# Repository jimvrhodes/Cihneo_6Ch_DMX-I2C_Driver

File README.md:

# Cineo_6CH_Driver
Cineo 6-Channel DC-DC Driver with both DMX and I2C Capability

Enclosed are all the projects for the Cineo 6-Channel Driver
1) PSoC Creator Project, source code (plus PSoC Creator install for verision 4.1, please do not upgrade!)
2) Eagle Board and Schematic Files
3) Gerber files for the Rev. A release
4) HEX files for production, PSoC Programmer Instructions

There are also two other code projects for the I2C Test Utility
a) Cineo_cHUB_I2C_Tester
b) Cineo_TestGUI
These two pieces of software utilize the DMXcHUB as the I2C master, and connects a user GUI with 6 sliders to the driver for control of the 6 channels.

All of these have been verified.
Jim Rhodes
NED
5-2-2020

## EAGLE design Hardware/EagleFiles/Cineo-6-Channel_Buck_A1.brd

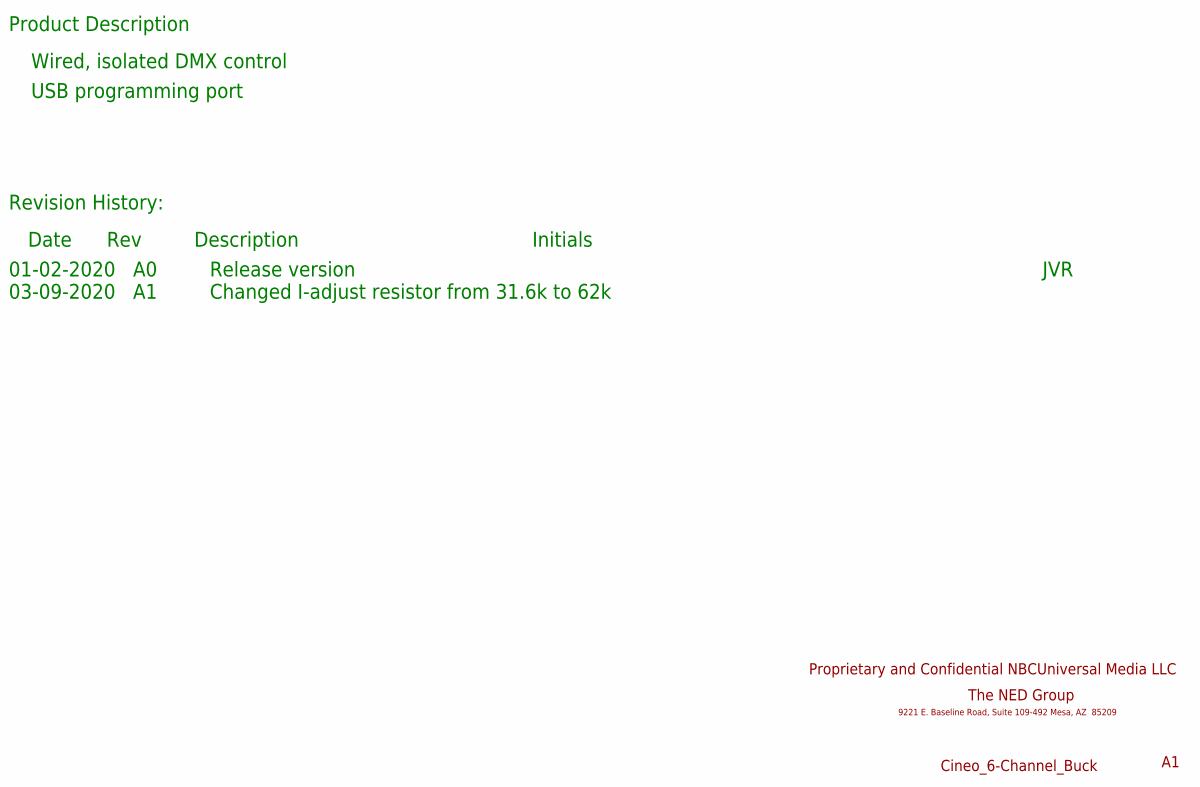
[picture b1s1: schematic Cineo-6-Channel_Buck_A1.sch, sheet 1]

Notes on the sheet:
Cineo_6-Channel_Buck
Product Description
Revision History:
Date Rev Description Initials
01-02-2020 A0 Release version
Wired, isolated DMX control
USB programming port
The NED Group
9221 E. Baseline Road, Suite 109-492 Mesa, AZ 85209
Proprietary and Confidential NBCUniversal Media LLC
JVR
03-09-2020 A1 Changed I-adjust resistor from 31.6k to 62k

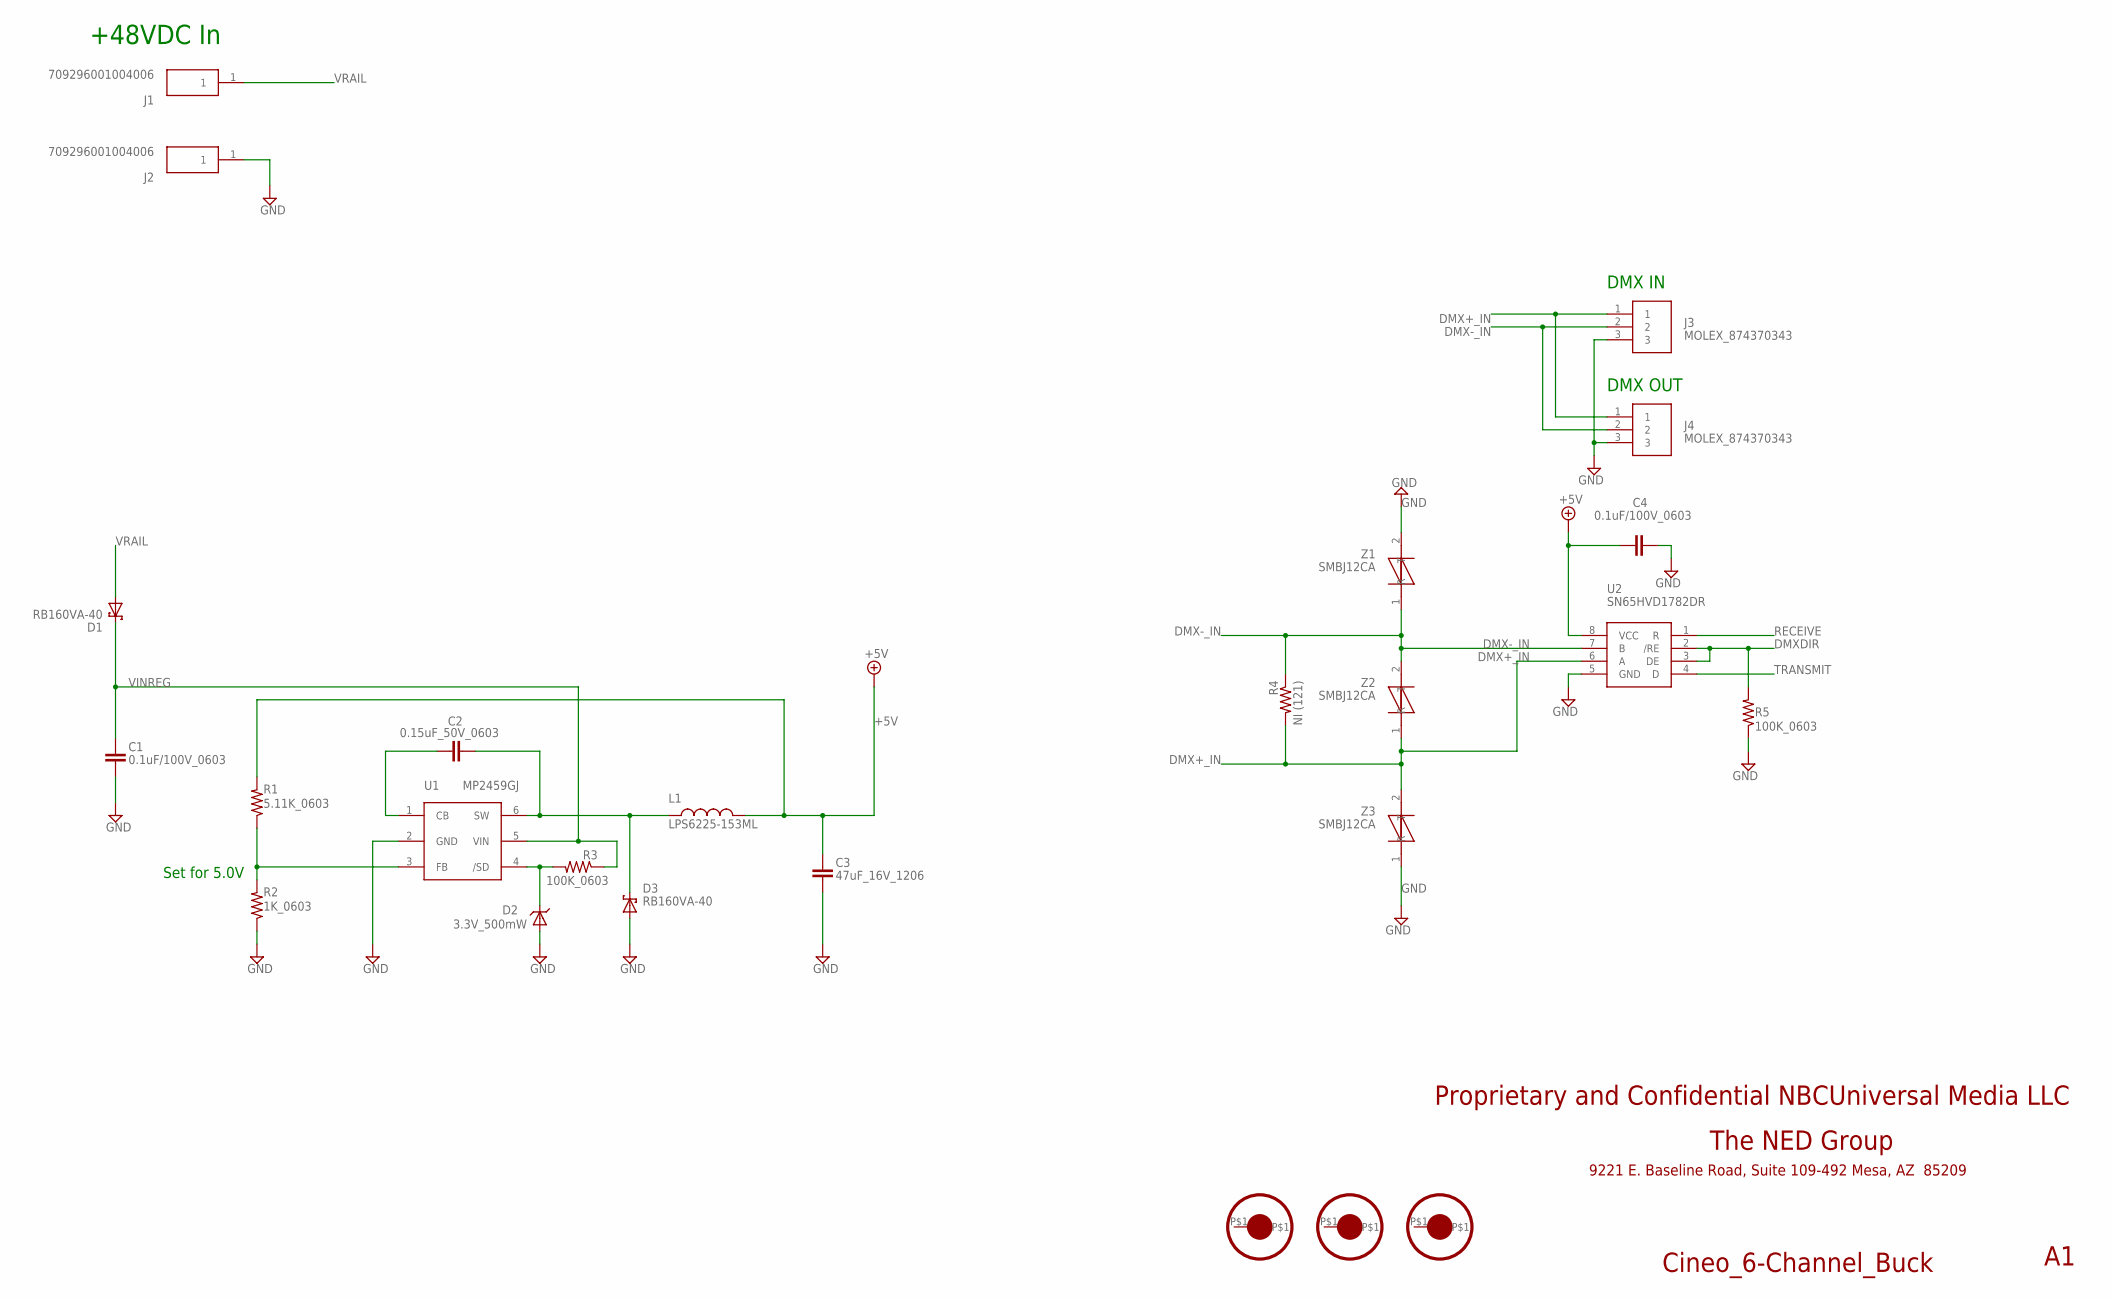
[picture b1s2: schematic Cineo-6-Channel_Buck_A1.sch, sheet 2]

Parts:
C1, C4: 0.1uF/100V_0603; C0603
C2: 0.15uF_50V_0603; C0603
C3: 47uF_16V_1206; C1206
D1, D3: RB160VA-40; TUMD2
D2: 3.3V_500mW; SOD-123
FID1, FID2, FID3: FIDUCIALSSMALLER; FIDUCIAL_1MMX3MM
J1, J2: 709296001004006; AVX_709296001004006
J3, J4: MOLEX_874370343
L1: LPS6225-153ML; COILCRAFT_LPS6235
R1: 5.11K_0603; R0603
R2: 1K_0603; R0603
R3, R5: 100K_0603; R0603
R4: NI (121); R0603
U1: MP2459GJ; TSOT_23-6
U2: SN65HVD1782DR; SO-8
Z1, Z2, Z3: SMBJ12CA; SMBJ

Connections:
+5V: C3.1, C4.1, L1.2, R1.2, U2.8 (VCC); also elsewhere on the board
DMX+_IN: J3.1, J4.1, R4.2, U2.6 (A), Z2.1 (R), Z3.2 (T)
DMX-_IN: J3.2, J4.2, R4.1, U2.7 (B), Z1.1 (R), Z2.2 (T)
DMXDIR: R5.2, U2.2 (/RE), U2.3 (DE); also elsewhere on the board
GND: C1.2, C3.2, C4.2, D2.A, D3.A, J2.1, J3.3, J4.3, R2.1, R5.1, U1.2 (GND), U2.5 (GND), Z1.2 (T), Z3.1 (R); also elsewhere on the board
unnamed: C2.1, U1.1 (CB)
unnamed: C2.2, D3.C, L1.1, U1.6 (SW)
unnamed: R1.1, R2.2, U1.3 (FB)
unnamed: D2.C, R3.2, U1.4 (/SD)
RECEIVE: U2.1 (R); also elsewhere on the board
TRANSMIT: U2.4 (D); also elsewhere on the board
VINREG: C1.1, D1.C, R3.1, U1.5 (VIN)
VRAIL: D1.A, J1.1; also elsewhere on the board

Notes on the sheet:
Set for 5.0V
+48VDC In
Cineo_6-Channel_Buck
The NED Group
9221 E. Baseline Road, Suite 109-492 Mesa, AZ 85209
Proprietary and Confidential NBCUniversal Media LLC
DMX IN
DMX OUT

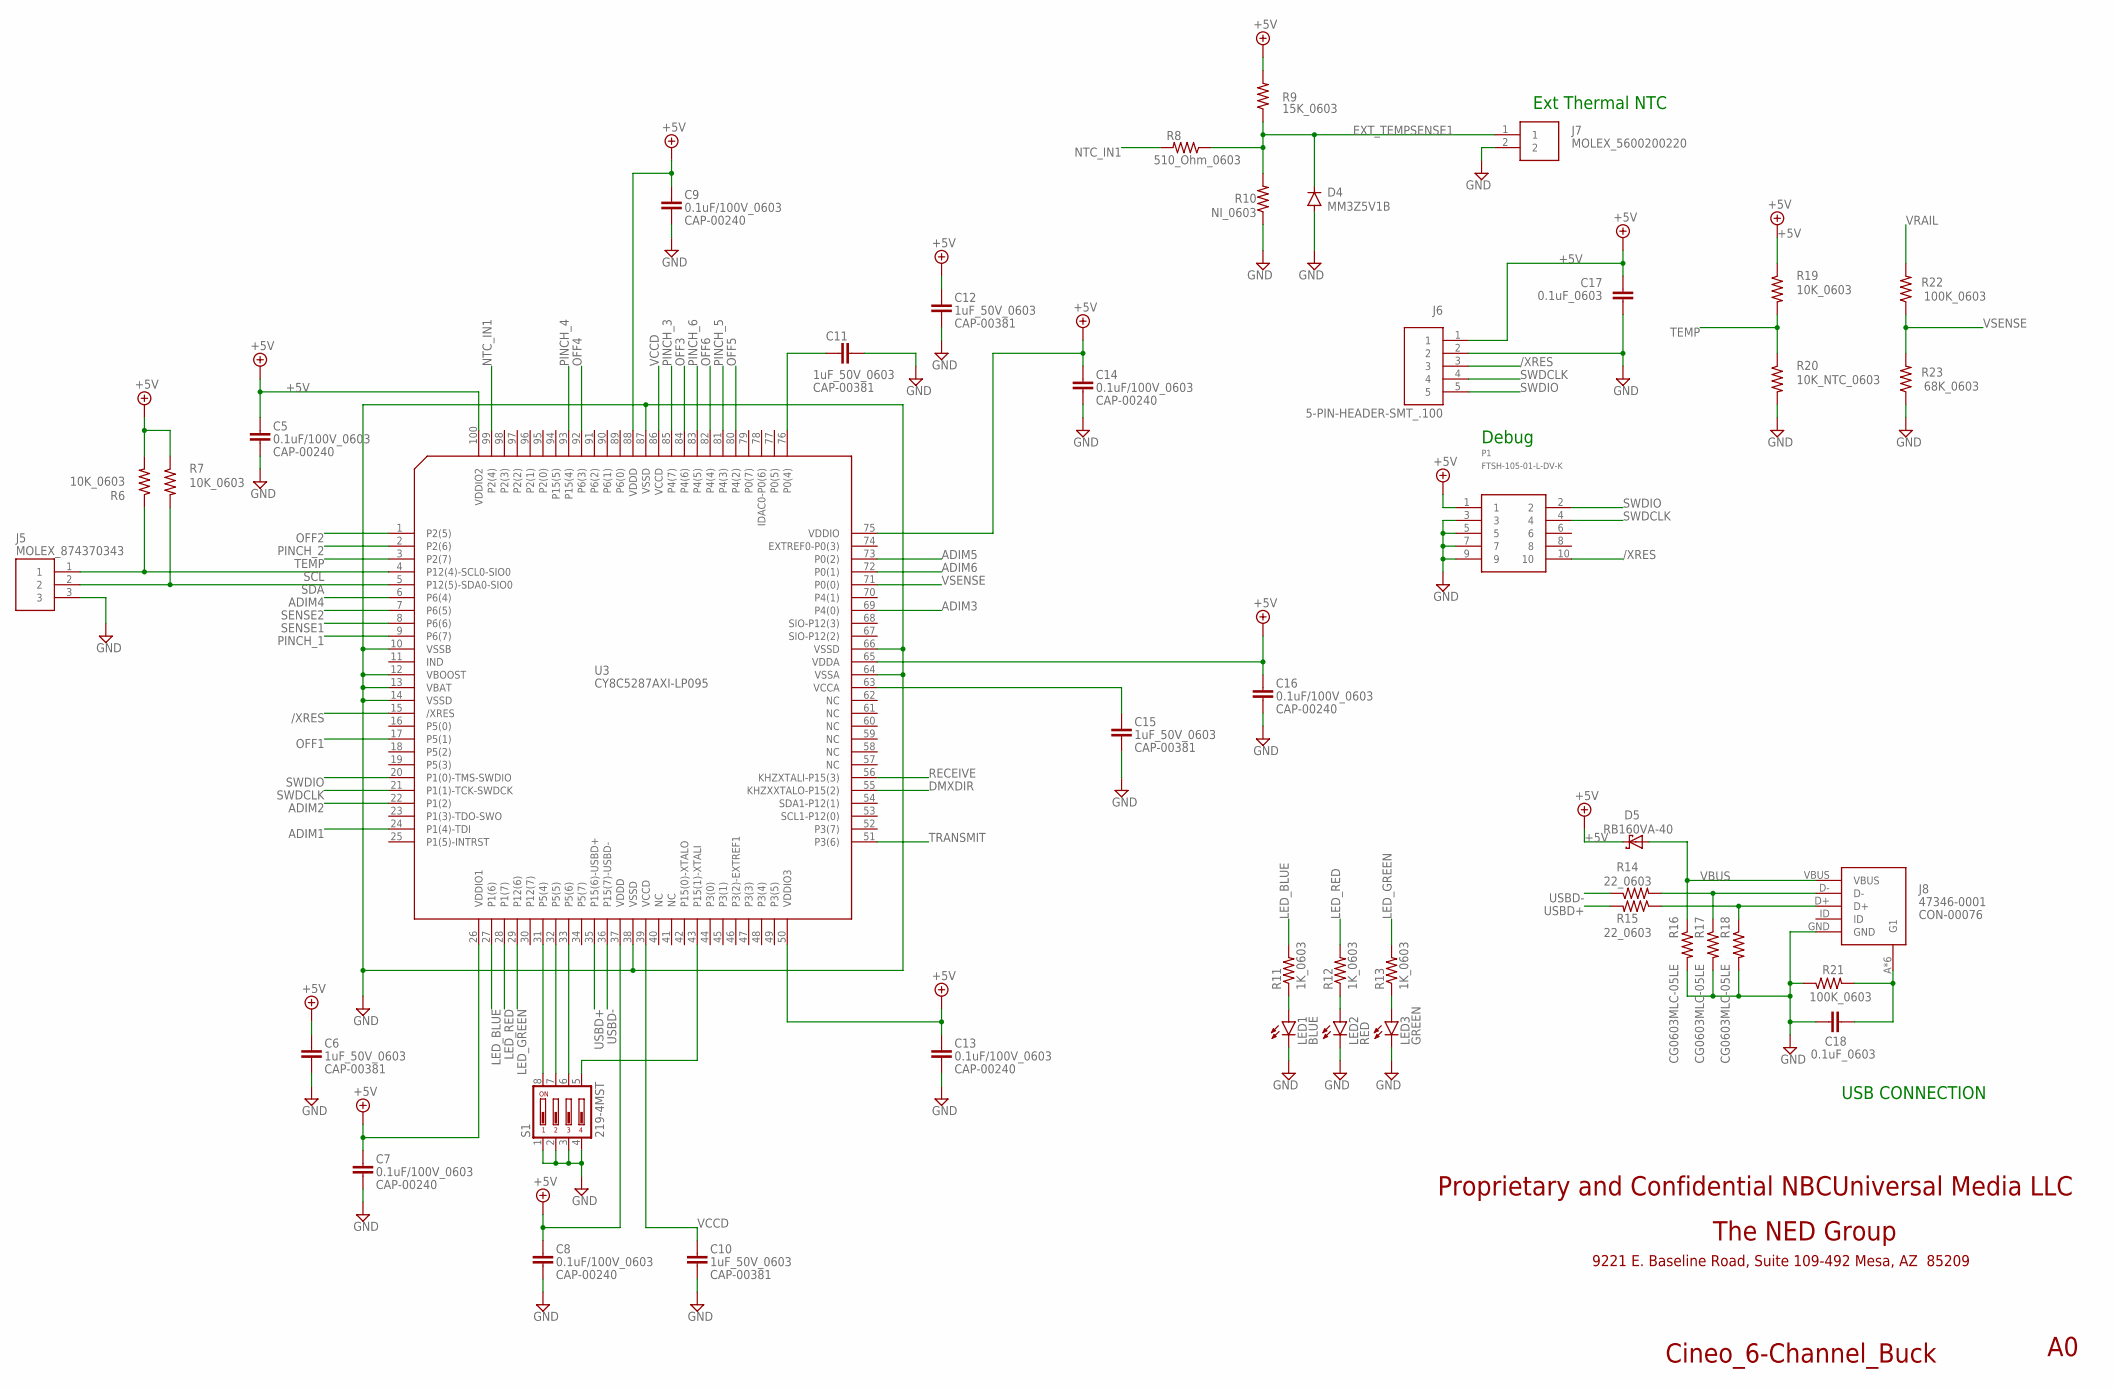
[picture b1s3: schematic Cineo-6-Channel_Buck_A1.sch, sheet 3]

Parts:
C5, C7, C8, C9, C13, C14, C16: 0.1uF/100V_0603; C0603
C6, C10, C11, C12, C15: 1uF_50V_0603; C0603
C17, C18: 0.1uF_0603; C0603
D4: MM3Z5V1B; SOD323-R
D5: RB160VA-40; TUMD2
J5: MOLEX_874370343
J6: 5-PIN-HEADER-SMT_.100; 5-PIN_SMT_.100
J7: MOLEX_5600200220
J8: 47346-0001; MOLEX_47346
LED1: BLUE; CHIPLED_0805
LED2: RED; CHIPLED_0805
LED3: GREEN; CHIPLED_0805
P1: FTSH-105-01-L-DV-K; SAMTEC_FTSH-105-01-L-DV-K
R6, R7, R19: 10K_0603; R0603
R8: 510_Ohm_0603; R0603
R9: 15K_0603; R0603
R10: NI_0603; R0603
R11, R12, R13: 1K_0603; R0603
R14, R15: 22_0603; R0603
R16, R17, R18: CG0603MLC-05LE; R0603
R20: 10K_NTC_0603; R0603
R21, R22: 100K_0603; R0603
R23: 68K_0603; R0603
S1: 219-4MST; CTS-219-04
U3: CY8C5287AXI-LP095; TQFP100

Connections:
+5V: C5.2, C6.2, C7.2, C8.2, C9.2, C12.2, C13.2, C14.2, C16.2, C17.1, D5.C, J6.1, P1.1, R6.2, R7.1, R9.2, R19.1, U3.26 (VDDIO1), U3.37 (VDDD), U3.50 (VDDIO3), U3.65 (VDDA), U3.75 (VDDIO), U3.88 (VDDD), U3.100 (VDDIO2); also elsewhere on the board
/XRES: J6.3, P1.10, U3.15 (/XRES)
ADIM1: U3.24 (P1(4)-TDI); also elsewhere on the board
ADIM2: U3.22 (P1(2)); also elsewhere on the board
ADIM3: U3.69 (P4(0)); also elsewhere on the board
ADIM4: U3.6 (P6(4)); also elsewhere on the board
ADIM5: U3.73 (P0(2)); also elsewhere on the board
ADIM6: U3.72 (P0(1)); also elsewhere on the board
DMXDIR: U3.55 (KHZXXTALO-P15(2)); also elsewhere on the board
EXT_TEMPSENSE1: D4.C, J7.1, R8.1, R9.1, R10.2
GND: C5.1, C6.1, C7.1, C8.1, C9.1, C10.1, C11.1, C12.1, C13.1, C14.1, C15.1, C16.1, C17.2, C18.2, D4.A, J5.3, J6.2, J7.2, J8.GND, LED1.C, LED2.C, LED3.C, P1.3, P1.5, P1.7, P1.9, R10.1, R16.2, R17.2, R18.2, R20.2, R21.1, R23.1, S1.1, S1.2, S1.3, S1.4, U3.10 (VSSB), U3.12 (VBOOST), U3.13 (VBAT), U3.14 (VSSD), U3.38 (VSSD), U3.64 (VSSA), U3.66 (VSSD), U3.87 (VSSD); also elsewhere on the board
LED_BLUE: R11.2, U3.27 (P1(6))
LED_GREEN: R13.2, U3.29 (P12(6))
LED_RED: R12.2, U3.28 (P1(7))
unnamed: C15.2, U3.63 (VCCA)
unnamed: S1.8, U3.31 (P5(4))
unnamed: S1.7, U3.32 (P5(5))
unnamed: C11.2, U3.76 (P0(4))
unnamed: S1.6, U3.33 (P5(6))
unnamed: S1.5, U3.43 (P15(1)-XTALI)
unnamed: LED3.A, R13.1
unnamed: LED2.A, R12.1
unnamed: J8.D-, R14.2, R17.1
unnamed: J8.D+, R15.1, R18.1
unnamed: C18.1, J8.A (G1), J8.B (G1), J8.G1, J8.S2 (G1), J8.S3 (G1), J8.S4 (G1), R21.2
unnamed: LED1.A, R11.1
NTC_IN1: R8.2, U3.99 (P2(4))
OFF1: U3.17 (P5(1)); also elsewhere on the board
OFF2: U3.1 (P2(5)); also elsewhere on the board
OFF3: U3.84 (P4(6)); also elsewhere on the board
OFF4: U3.92 (P6(3)); also elsewhere on the board
OFF5: U3.80 (P4(2)); also elsewhere on the board
OFF6: U3.82 (P4(4)); also elsewhere on the board
PINCH_1: U3.9 (P6(7)); also elsewhere on the board
PINCH_2: U3.2 (P2(6)); also elsewhere on the board
PINCH_3: U3.85 (P4(7)); also elsewhere on the board
PINCH_4: U3.93 (P15(4)); also elsewhere on the board
PINCH_5: U3.81 (P4(3)); also elsewhere on the board
PINCH_6: U3.83 (P4(5)); also elsewhere on the board
RECEIVE: U3.56 (KHZXTALI-P15(3)); also elsewhere on the board
SCL: J5.1, R6.1, U3.4 (P12(4)-SCL0-SIO0)
SDA: J5.2, R7.2, U3.5 (P12(5)-SDA0-SIO0)
SENSE1: U3.8 (P6(6)); also elsewhere on the board
SENSE2: U3.7 (P6(5)); also elsewhere on the board
SWDCLK: J6.4, P1.4, U3.21 (P1(1)-TCK-SWDCK)
SWDIO: J6.5, P1.2, U3.20 (P1(0)-TMS-SWDIO)
TEMP: R19.2, R20.1, U3.3 (P2(7))
TRANSMIT: U3.51 (P3(6)); also elsewhere on the board
USBD+: R15.2, U3.35 (P15(6)-USBD+)
USBD-: R14.1, U3.36 (P15(7)-USBD-)
VBUS: D5.A, J8.VBUS, R16.1
VCCD: C10.2, U3.39 (VCCD), U3.86 (VCCD)
VRAIL: R22.2; also elsewhere on the board
VSENSE: R22.1, R23.2, U3.71 (P0(0))

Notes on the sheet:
Debug
USB CONNECTION
Cineo_6-Channel_Buck
The NED Group
9221 E. Baseline Road, Suite 109-492 Mesa, AZ 85209
Proprietary and Confidential NBCUniversal Media LLC
Ext Thermal NTC

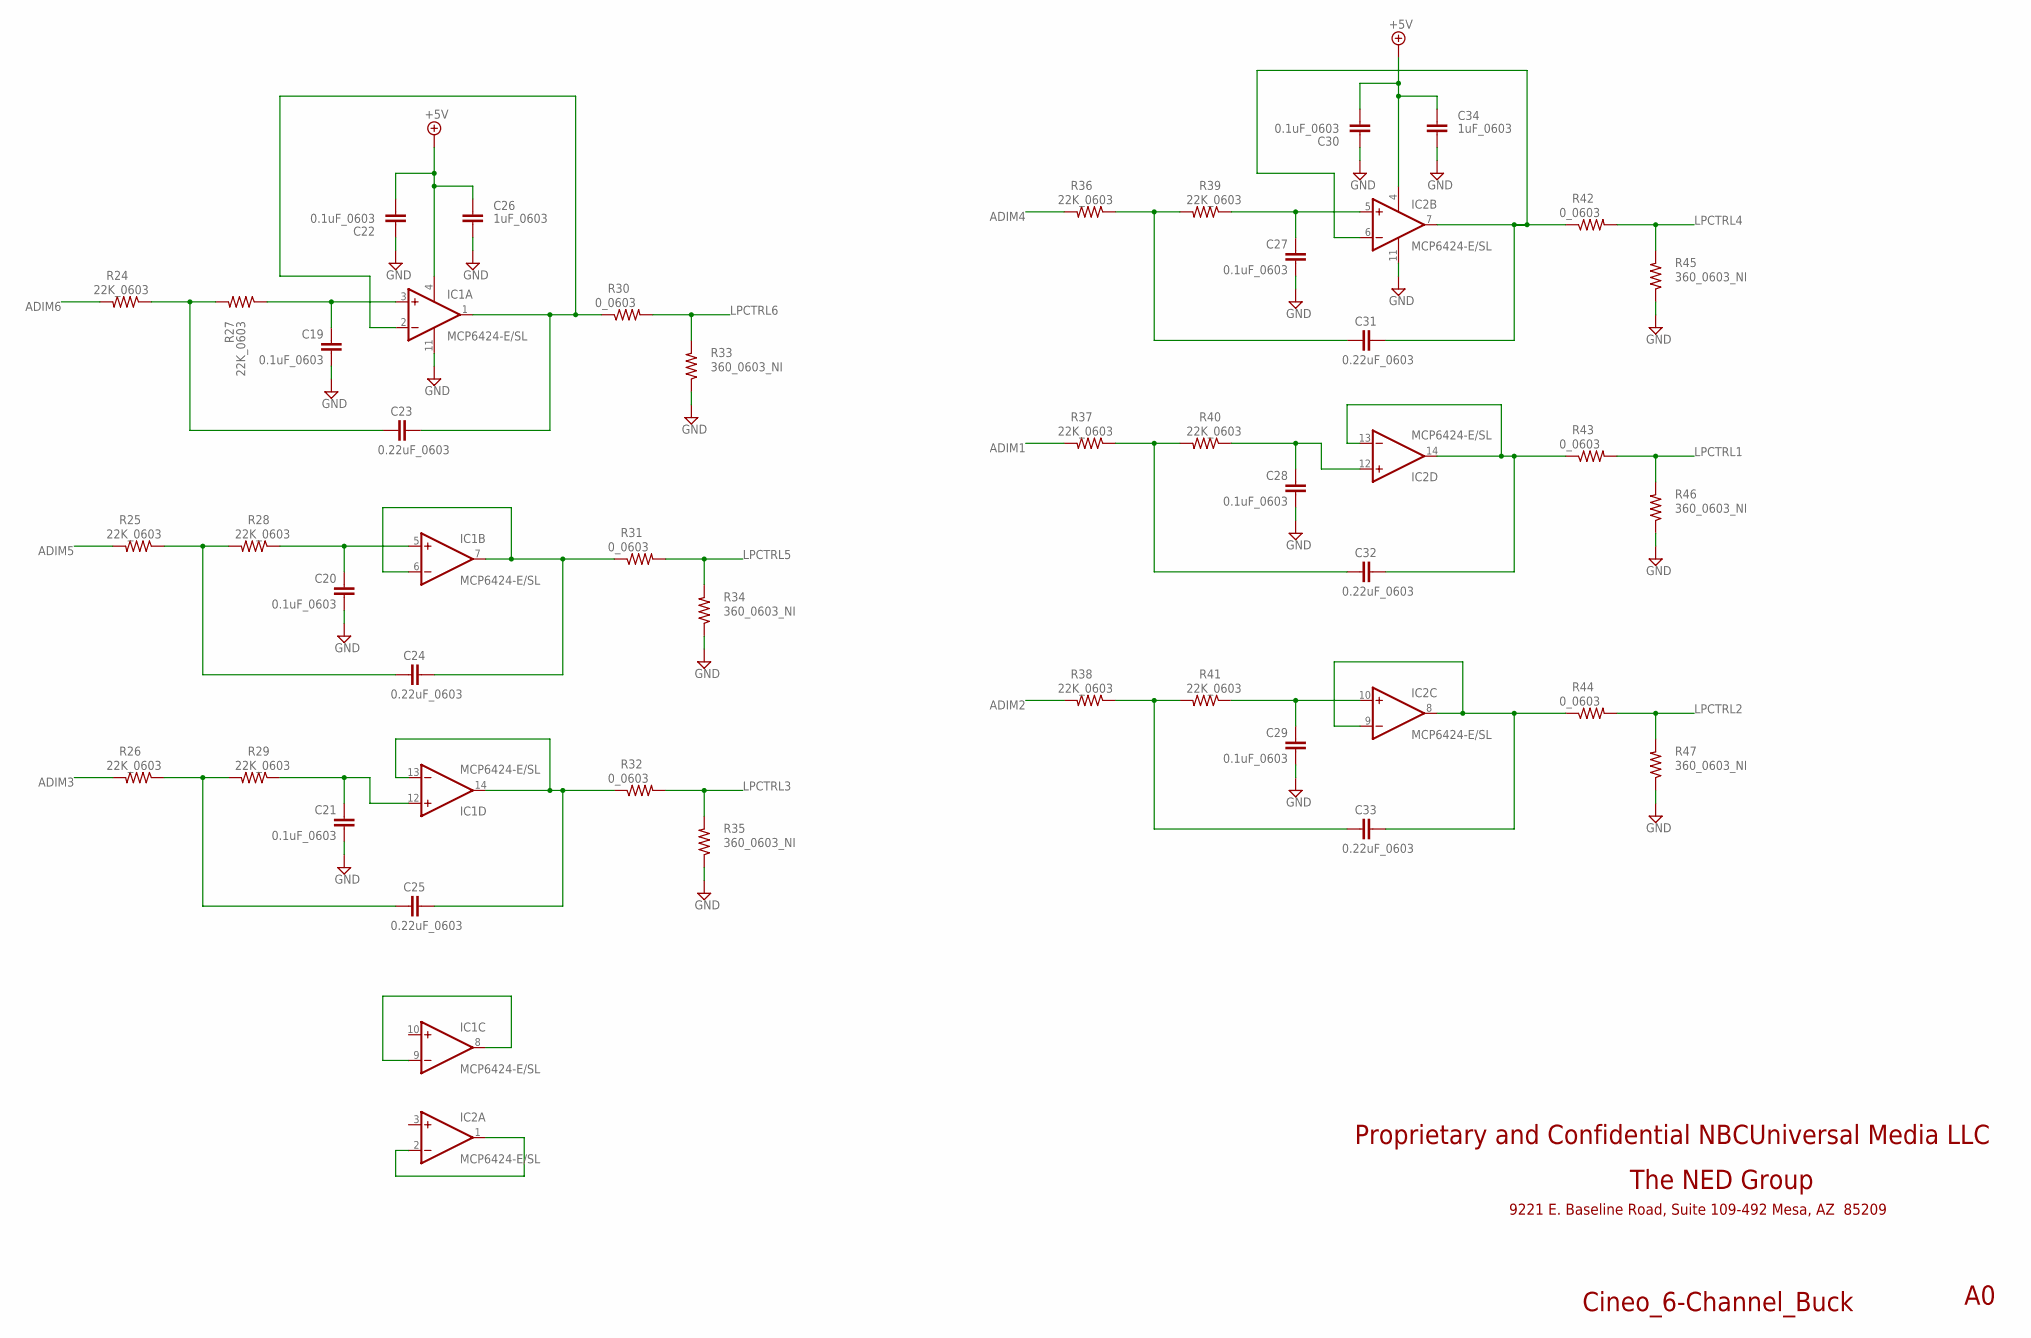
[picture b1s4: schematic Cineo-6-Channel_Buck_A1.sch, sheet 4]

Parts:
C19, C20, C21, C22, C27, C28, C29, C30: 0.1uF_0603; C0603
C23, C24, C25, C31, C32, C33: 0.22uF_0603; C0603
C26, C34: 1uF_0603; C0603
IC1, IC2: MCP6424-E/SL; SO14
R24, R25, R26, R27, R28, R29, R36, R37, R38, R39, R40, R41: 22K_0603; R0603
R30, R31, R32, R42, R43, R44: 0_0603; R0603
R33, R34, R35, R45, R46, R47: 360_0603_NI; R0603

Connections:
+5V: C22.1, C26.2, C30.1, C34.2, IC1.4 (V+), IC2.4 (V+); also elsewhere on the board
ADIM1: R37.2; also elsewhere on the board
ADIM2: R38.2; also elsewhere on the board
ADIM3: R26.2; also elsewhere on the board
ADIM4: R36.2; also elsewhere on the board
ADIM5: R25.2; also elsewhere on the board
ADIM6: R24.2; also elsewhere on the board
GND: C19.1, C20.1, C21.1, C22.2, C26.1, C27.1, C28.1, C29.1, C30.2, C34.1, IC1.11 (V-), IC2.11 (V-), R33.1, R34.1, R35.1, R45.1, R46.1, R47.1; also elsewhere on the board
LPCTRL1: R43.2, R46.2; also elsewhere on the board
LPCTRL2: R44.2, R47.2; also elsewhere on the board
LPCTRL3: R32.2, R35.2; also elsewhere on the board
LPCTRL4: R42.2, R45.2; also elsewhere on the board
LPCTRL5: R31.2, R34.2; also elsewhere on the board
LPCTRL6: R30.2, R33.2; also elsewhere on the board
unnamed: C24.1, R25.1, R28.2
unnamed: C20.2, IC1.5 (+IN), R28.1
unnamed: C24.2, IC1.6 (-IN), IC1.7 (OUT), R31.1
unnamed: C23.1, R24.1, R27.2
unnamed: C19.2, IC1.3 (+IN), R27.1
unnamed: IC1.8 (OUT), IC1.9 (-IN)
unnamed: C25.1, R26.1, R29.2
unnamed: C21.2, IC1.12 (+IN), R29.1
unnamed: C25.2, IC1.13 (-IN), IC1.14 (OUT), R32.1
unnamed: IC2.1 (OUT), IC2.2 (-IN)
unnamed: C23.2, IC1.1 (OUT), IC1.2 (-IN), R30.1
unnamed: C31.1, R36.1, R39.2
unnamed: C27.2, IC2.5 (+IN), R39.1
unnamed: C31.2, IC2.6 (-IN), IC2.7 (OUT), R42.1
unnamed: C33.1, R38.1, R41.2
unnamed: C29.2, IC2.10 (+IN), R41.1
unnamed: C33.2, IC2.8 (OUT), IC2.9 (-IN), R44.1
unnamed: C32.1, R37.1, R40.2
unnamed: C28.2, IC2.12 (+IN), R40.1
unnamed: C32.2, IC2.13 (-IN), IC2.14 (OUT), R43.1

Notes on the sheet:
Cineo_6-Channel_Buck
The NED Group
9221 E. Baseline Road, Suite 109-492 Mesa, AZ 85209
Proprietary and Confidential NBCUniversal Media LLC

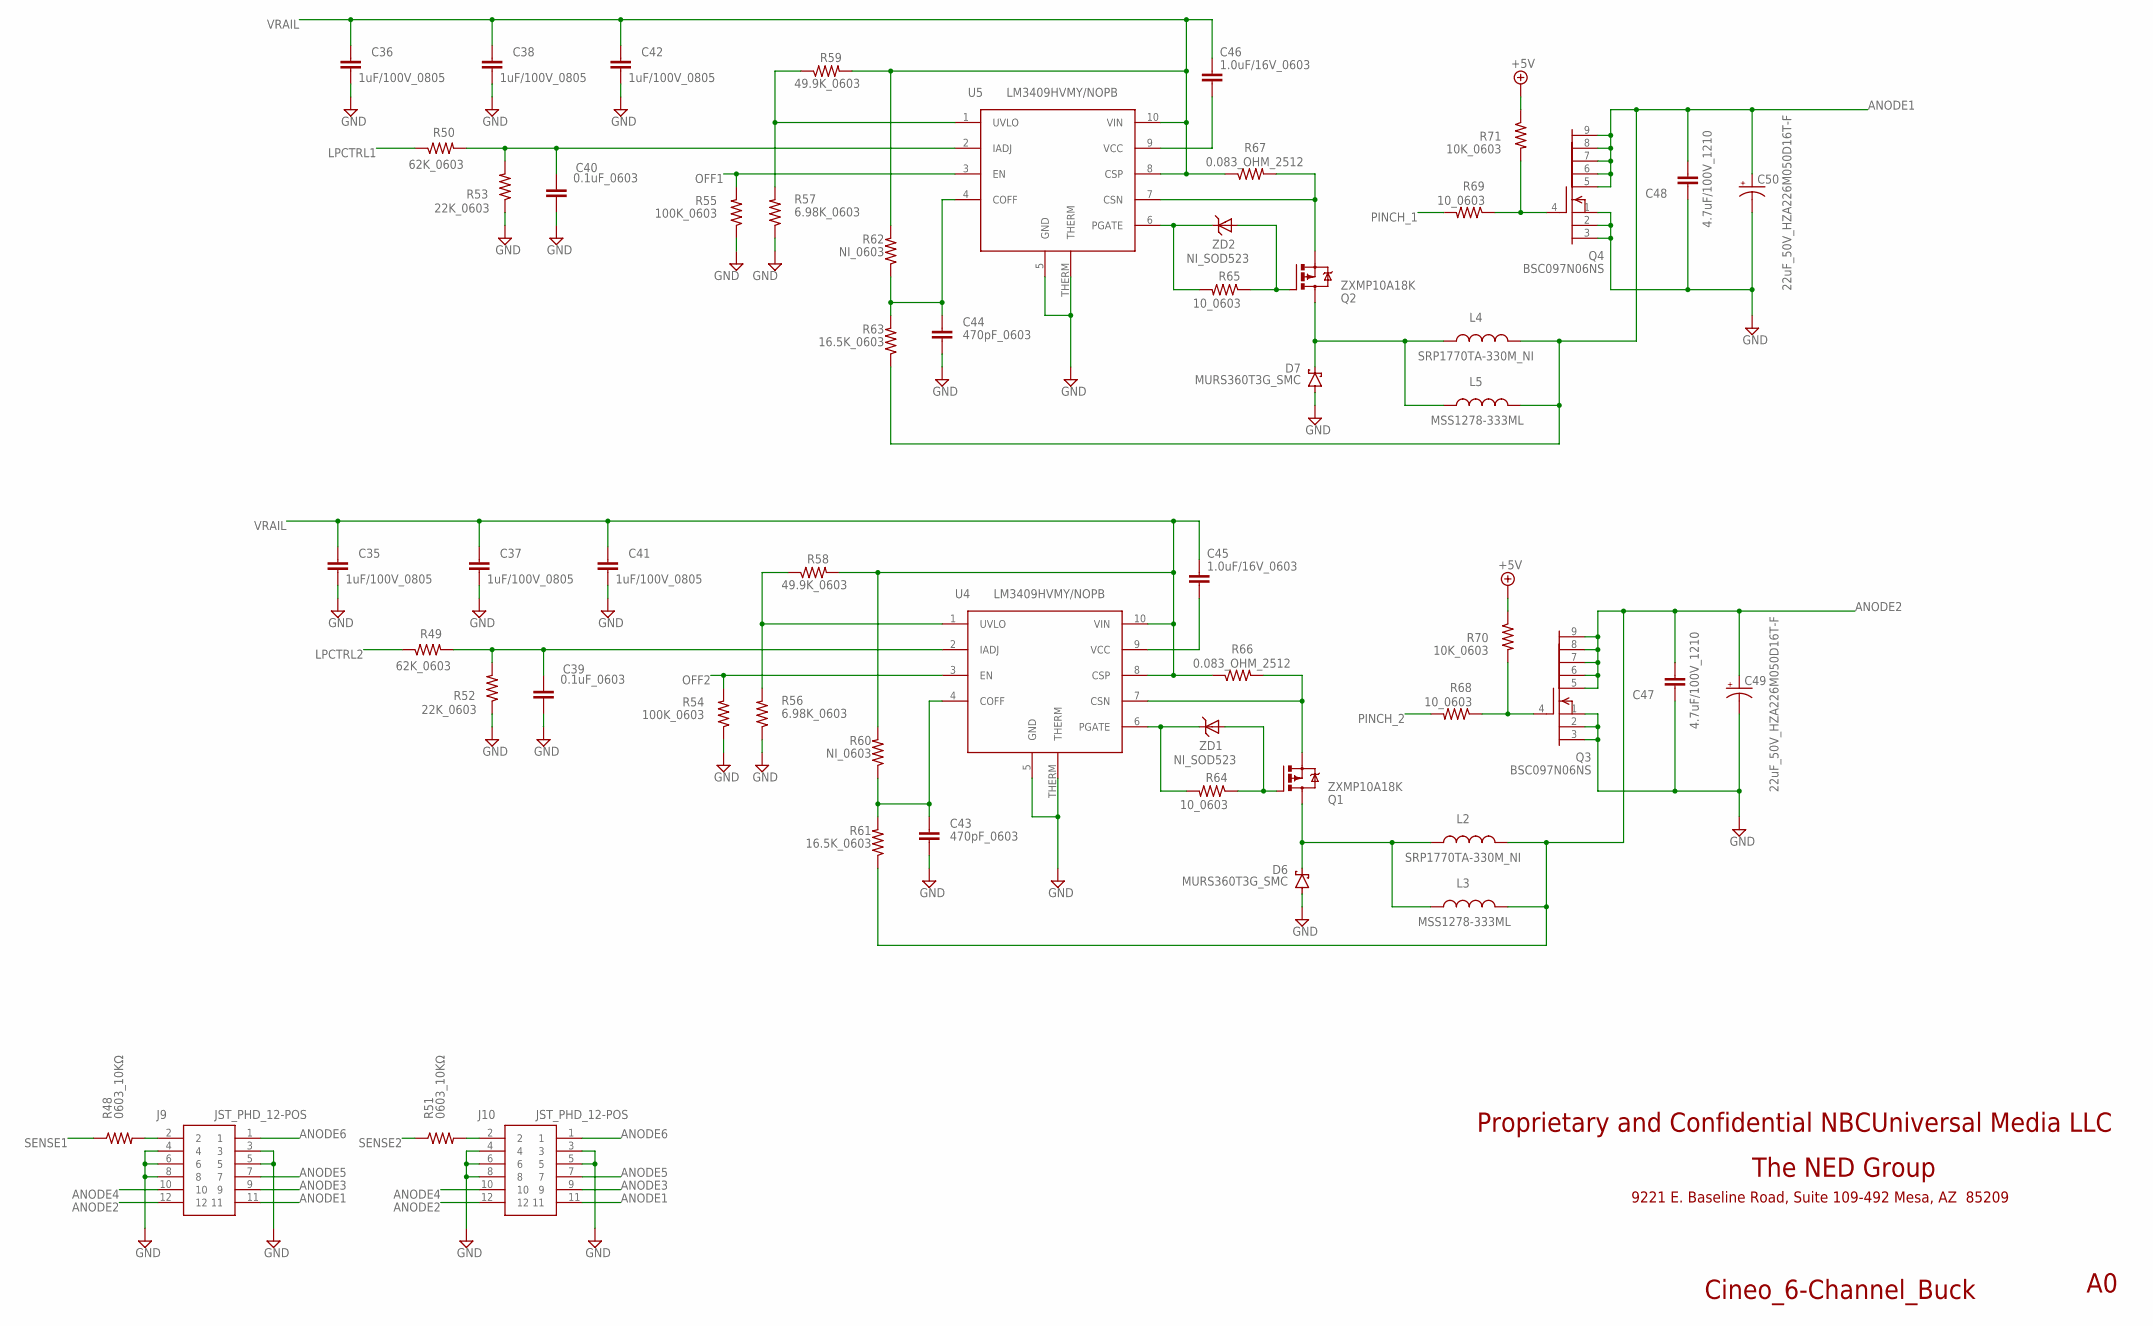
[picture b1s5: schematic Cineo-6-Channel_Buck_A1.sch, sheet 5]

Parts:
C35, C36, C37, C38, C41, C42: 1uF/100V_0805; C0805
C39, C40: 0.1uF_0603; C0603
C43, C44: 470pF_0603; C0603
C45, C46: 1.0uF/16V_0603; C0603
C47, C48: 4.7uF/100V_1210; C1210
C49, C50: 22uF_50V_HZA226M050D16T-F; PANASONIC_D
D6, D7: MURS360T3G_SMC; SMC
J9, J10: JST_PHD_12-POS
L2, L4: SRP1770TA-330M_NI; BOURNS_SRP1770TA
L3, L5: MSS1278-333ML; MSS1260
Q1, Q2: ZXMP10A18K; DPAK
Q3, Q4: BSC097N06NS; SO-8_POWERPAC
R48, R51: 0603_10KΩ; R0603
R49, R50: 62K_0603; R0603
R52, R53: 22K_0603; R0603
R54, R55: 100K_0603; R0603
R56, R57: 6.98K_0603; R0603
R58, R59: 49.9K_0603; R0603
R60, R62: NI_0603; R0603
R61, R63: 16.5K_0603; R0603
R64, R65, R68, R69: 10_0603; R0603
R66, R67: 0.083_OHM_2512; R2512
R70, R71: 10K_0603; R0603
U4, U5: LM3409HVMY/NOPB; MSOP10-THERMALENHANCED
ZD1, ZD2: NI_SOD523; SOD-523

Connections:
+5V: R70.1, R71.1; also elsewhere on the board
ANODE1: C48.2, C50.+, J9.11, J10.11, L4.P$2 (2), L5.2, Q4.5 (D), Q4.6 (D1), Q4.7 (D2), Q4.8 (D3), Q4.9 (D4), R63.1
ANODE2: C47.2, C49.+, J9.12, J10.12, L2.P$2 (2), L3.2, Q3.5 (D), Q3.6 (D1), Q3.7 (D2), Q3.8 (D3), Q3.9 (D4), R61.1
ANODE3: J9.9, J10.9; also elsewhere on the board
ANODE4: J9.10, J10.10; also elsewhere on the board
ANODE5: J9.7, J10.7; also elsewhere on the board
ANODE6: J9.1, J10.1; also elsewhere on the board
GND: C35.2, C36.2, C37.2, C38.2, C39.1, C40.1, C41.2, C42.2, C43.1, C44.1, C47.1, C48.1, C49.-, C50.-, D6.A, D7.A, J9.3, J9.4, J9.5, J9.6, J9.8, J10.3, J10.4, J10.5, J10.6, J10.8, Q3.1 (S), Q3.2 (S1), Q3.3 (S2), Q4.1 (S), Q4.2 (S1), Q4.3 (S2), R52.1, R53.1, R54.1, R55.1, R56.1, R57.1, U4.5 (GND), U4.THERM, U5.5 (GND), U5.THERM; also elsewhere on the board
LPCTRL1: R50.1; also elsewhere on the board
LPCTRL2: R49.1; also elsewhere on the board
unnamed: C44.2, R62.1, R63.2, U5.4 (COFF)
unnamed: C46.1, U5.9 (VCC)
unnamed: Q2.E (S), R67.2, U5.7 (CSN)
unnamed: Q2.B (G), R65.1, ZD2.A
unnamed: R65.2, U5.6 (PGATE), ZD2.C
unnamed: D7.C, L4.P$1 (1), L5.1, Q2.C (D)
unnamed: J9.2, R48.2
unnamed: J10.2, R51.2
unnamed: R56.2, R58.1, U4.1 (UVLO)
unnamed: C39.2, R49.2, R52.2, U4.2 (IADJ)
unnamed: Q3.4 (G), R68.1, R70.2
unnamed: C43.2, R60.1, R61.2, U4.4 (COFF)
unnamed: C45.1, U4.9 (VCC)
unnamed: Q1.E (S), R66.2, U4.7 (CSN)
unnamed: Q1.B (G), R64.1, ZD1.A
unnamed: R64.2, U4.6 (PGATE), ZD1.C
unnamed: D6.C, L2.P$1 (1), L3.1, Q1.C (D)
unnamed: R57.2, R59.1, U5.1 (UVLO)
unnamed: C40.2, R50.2, R53.2, U5.2 (IADJ)
unnamed: Q4.4 (G), R69.1, R71.2
OFF1: R55.2, U5.3 (EN); also elsewhere on the board
OFF2: R54.2, U4.3 (EN); also elsewhere on the board
PINCH_1: R69.2; also elsewhere on the board
PINCH_2: R68.2; also elsewhere on the board
SENSE1: R48.1; also elsewhere on the board
SENSE2: R51.1; also elsewhere on the board
VRAIL: C35.1, C36.1, C37.1, C38.1, C41.1, C42.1, C45.2, C46.2, R58.2, R59.2, R60.2, R62.2, R66.1, R67.1, U4.8 (CSP), U4.10 (VIN), U5.8 (CSP), U5.10 (VIN); also elsewhere on the board

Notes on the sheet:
Cineo_6-Channel_Buck
The NED Group
9221 E. Baseline Road, Suite 109-492 Mesa, AZ 85209
Proprietary and Confidential NBCUniversal Media LLC

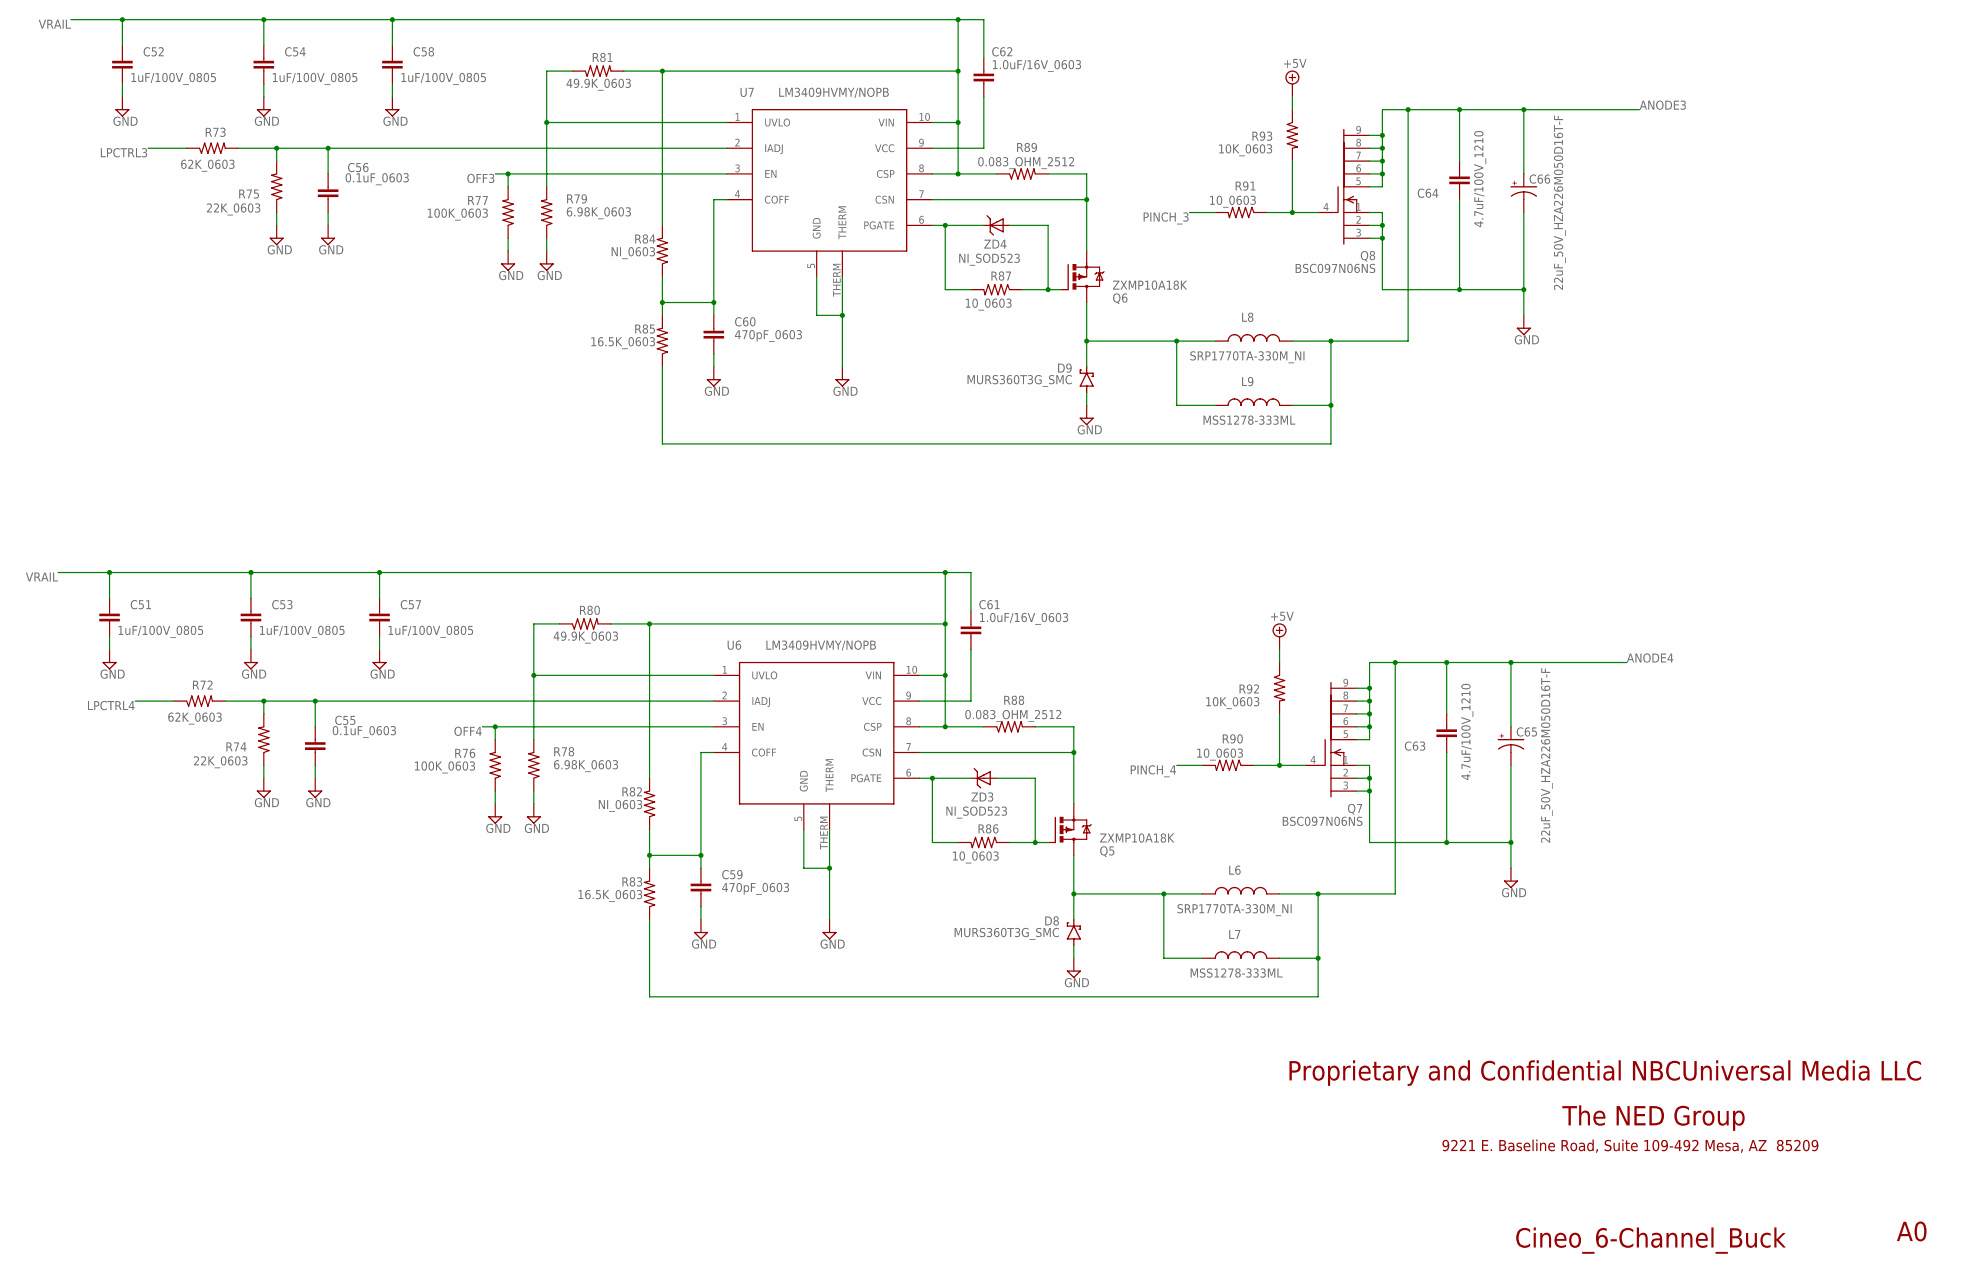
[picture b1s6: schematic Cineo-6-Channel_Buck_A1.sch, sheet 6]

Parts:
C51, C52, C53, C54, C57, C58: 1uF/100V_0805; C0805
C55, C56: 0.1uF_0603; C0603
C59, C60: 470pF_0603; C0603
C61, C62: 1.0uF/16V_0603; C0603
C63, C64: 4.7uF/100V_1210; C1210
C65, C66: 22uF_50V_HZA226M050D16T-F; PANASONIC_D
D8, D9: MURS360T3G_SMC; SMC
L6, L8: SRP1770TA-330M_NI; BOURNS_SRP1770TA
L7, L9: MSS1278-333ML; MSS1260
Q5, Q6: ZXMP10A18K; DPAK
Q7, Q8: BSC097N06NS; SO-8_POWERPAC
R72, R73: 62K_0603; R0603
R74, R75: 22K_0603; R0603
R76, R77: 100K_0603; R0603
R78, R79: 6.98K_0603; R0603
R80, R81: 49.9K_0603; R0603
R82, R84: NI_0603; R0603
R83, R85: 16.5K_0603; R0603
R86, R87, R90, R91: 10_0603; R0603
R88, R89: 0.083_OHM_2512; R2512
R92, R93: 10K_0603; R0603
U6, U7: LM3409HVMY/NOPB; MSOP10-THERMALENHANCED
ZD3, ZD4: NI_SOD523; SOD-523

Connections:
+5V: R92.1, R93.1; also elsewhere on the board
ANODE3: C64.2, C66.+, L8.P$2 (2), L9.2, Q8.5 (D), Q8.6 (D1), Q8.7 (D2), Q8.8 (D3), Q8.9 (D4), R85.1; also elsewhere on the board
ANODE4: C63.2, C65.+, L6.P$2 (2), L7.2, Q7.5 (D), Q7.6 (D1), Q7.7 (D2), Q7.8 (D3), Q7.9 (D4), R83.1; also elsewhere on the board
GND: C51.2, C52.2, C53.2, C54.2, C55.1, C56.1, C57.2, C58.2, C59.1, C60.1, C63.1, C64.1, C65.-, C66.-, D8.A, D9.A, Q7.1 (S), Q7.2 (S1), Q7.3 (S2), Q8.1 (S), Q8.2 (S1), Q8.3 (S2), R74.1, R75.1, R76.1, R77.1, R78.1, R79.1, U6.5 (GND), U6.THERM, U7.5 (GND), U7.THERM; also elsewhere on the board
LPCTRL3: R73.1; also elsewhere on the board
LPCTRL4: R72.1; also elsewhere on the board
unnamed: R79.2, R81.1, U7.1 (UVLO)
unnamed: C56.2, R73.2, R75.2, U7.2 (IADJ)
unnamed: Q8.4 (G), R91.1, R93.2
unnamed: C60.2, R84.1, R85.2, U7.4 (COFF)
unnamed: C62.1, U7.9 (VCC)
unnamed: Q6.E (S), R89.2, U7.7 (CSN)
unnamed: Q6.B (G), R87.1, ZD4.A
unnamed: R87.2, U7.6 (PGATE), ZD4.C
unnamed: D9.C, L8.P$1 (1), L9.1, Q6.C (D)
unnamed: R78.2, R80.1, U6.1 (UVLO)
unnamed: C55.2, R72.2, R74.2, U6.2 (IADJ)
unnamed: Q7.4 (G), R90.1, R92.2
unnamed: C59.2, R82.1, R83.2, U6.4 (COFF)
unnamed: C61.1, U6.9 (VCC)
unnamed: Q5.E (S), R88.2, U6.7 (CSN)
unnamed: Q5.B (G), R86.1, ZD3.A
unnamed: R86.2, U6.6 (PGATE), ZD3.C
unnamed: D8.C, L6.P$1 (1), L7.1, Q5.C (D)
OFF3: R77.2, U7.3 (EN); also elsewhere on the board
OFF4: R76.2, U6.3 (EN); also elsewhere on the board
PINCH_3: R91.2; also elsewhere on the board
PINCH_4: R90.2; also elsewhere on the board
VRAIL: C51.1, C52.1, C53.1, C54.1, C57.1, C58.1, C61.2, C62.2, R80.2, R81.2, R82.2, R84.2, R88.1, R89.1, U6.8 (CSP), U6.10 (VIN), U7.8 (CSP), U7.10 (VIN); also elsewhere on the board

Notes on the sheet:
Cineo_6-Channel_Buck
The NED Group
9221 E. Baseline Road, Suite 109-492 Mesa, AZ 85209
Proprietary and Confidential NBCUniversal Media LLC
